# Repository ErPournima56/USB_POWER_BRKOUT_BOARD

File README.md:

# USB_POWER_BRKOUT_BOARD
This is a simple, compact USB power breakout board designed in KiCad. Useful for power access and USB-based embedded projects.

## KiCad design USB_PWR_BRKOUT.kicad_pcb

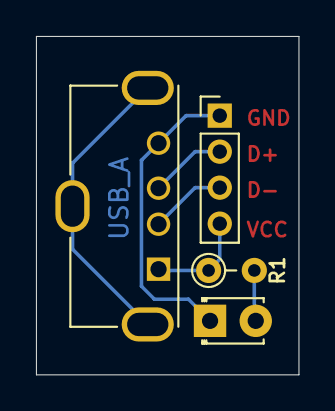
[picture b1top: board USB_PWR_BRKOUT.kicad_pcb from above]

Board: 2 copper layers, 14.6 x 18.8 mm, 4 parts (0 on the bottom side), 5 nets.

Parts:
D1: L1; LED_D1.8mm_W3.3mm_H2.4mm
J1: USB_A; USB_A_Molex_105057_Vertical
J2: Conn; PinHeader_1x04_P2.00mm_Vertical
R1: R; R_Axial_DIN0204_L3.6mm_D1.6mm_P2.54mm_Vertical

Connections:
/D+: J1.3 (D+), J2.2
/D-: J1.2 (D-), J2.3
/GND: D1.1 (K), J1.4 (GND), J2.1
/PWR: J1.1 (VBUS), J2.4, R1.1
unnamed: D1.2 (A), R1.2

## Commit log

2025-07-04 Add files via upload
    Kicad Files
